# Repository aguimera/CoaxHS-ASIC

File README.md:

View this project on [CADLAB.io](https://cadlab.io/project/27561). 

# CoaxHS-ASIC

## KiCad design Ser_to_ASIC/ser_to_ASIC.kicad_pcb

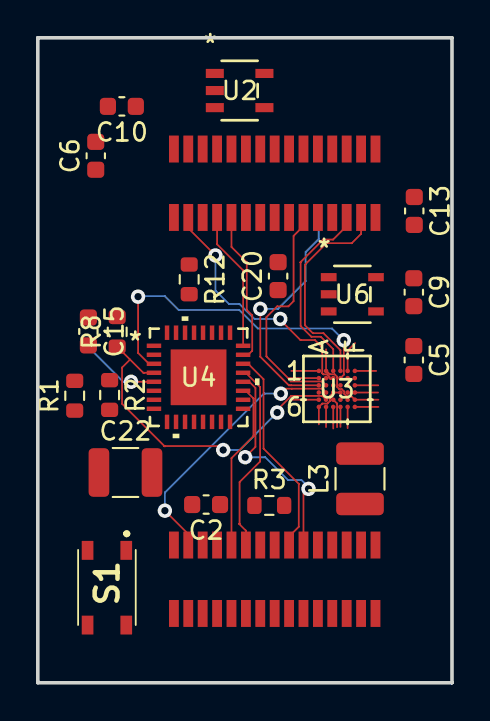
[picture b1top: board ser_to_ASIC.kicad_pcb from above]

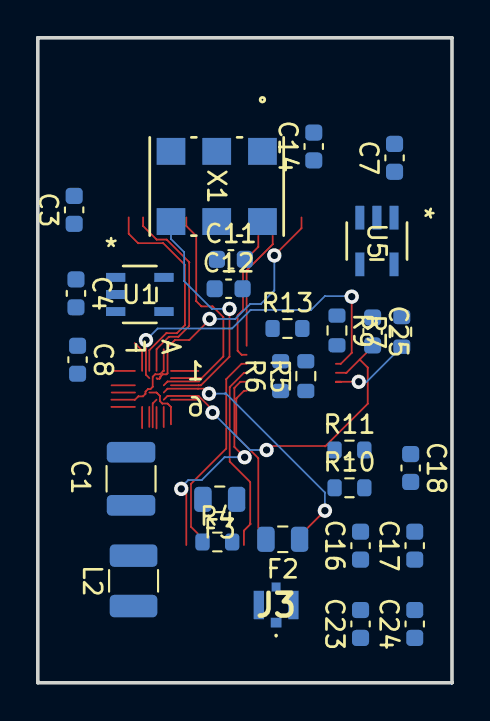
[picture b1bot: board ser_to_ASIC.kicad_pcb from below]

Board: 2 copper layers, 23.0 x 35.8 mm, 51 parts (29 on the bottom side), 47 nets.

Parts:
C1: 47uF; C_1210_3225Metric
C2, C12, C17, C24, C25: 0.1uF; C_0603_1608Metric
C3, C4, C5, C6, C7, C9, C11, C15, C16, C20, C23: 1uF; C_0603_1608Metric
C8, C10, C18: 10uF; C_0603_1608Metric
C13, C14: 0.01uF; C_0603_1608Metric
C22: 22uF; C_1210_3225Metric
F2, F3: 1000 ohm; Fuse_0805_2012Metric
J3: CONMHF4-SMD-G-T; CONMHF4SMDGT
J6, J200: MOLEX-524653071; J524653071_Board2Board
L2: 0.1 uF; L_1210_3225Metric
L3: 4.7 uF; L_1210_3225Metric
R1, R5, R10, R11: 10k; R_0603_1608Metric
R2: 100k; R_0603_1608Metric
R3, R4: 1k; R_0603_1608Metric
R6, R9, R12, R13: 0; R_0603_1608Metric
R7, R8: 4.7k; R_0603_1608Metric
S1: PTS810SJM250SMTRLFS; PTS810SJG250SMTRLFS
U1: ADP160AUJZ-1.2-R7; UJ_5_ADI
U2: ADP121-AUJZ12R7; UJ-5_ADI
U3: 10M02DCV36I7G; VBGA&slash_WLCSP36_A0p54_INT
U4: DS90UB913ATRTVJQ1; RTV32_3P1X3P1_TEX
U5: TC2015-1.8VCTTR; SOT-23-5_MC_MCH
U6: LT1761ES5-3.3-TRPBF; 05-08-1635_ADI
X1: EG-2102CA 100.0000M-PHPAL3; EG-2121CA_EPS

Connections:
+1V2: C6.1, U2.5 (VOUT), U3.B1 (VCC), U3.F5 (VCC)
+1V8: C5.1, C8.1, C11.1, C12.1, C14.1, C15.2, C16.1, C17.1, C20.1, C22.1, C23.1, C24.1, C25.2, R1.2, R5.2, U2.1 (VIN), U2.3 (EN), U4.10 (VDDPLL), U4.11 (VDDT), U4.14 (VDDCML), U4.25 (VDDIO), U4.28 (VDDD), U5.5
+3.3V: C7.1, C10.1, C13.1, R9.1, R10.1, R11.1, U3.A1 (VCCA3), U3.A6 (VCCA2), U3.C4 (VCCIO1_2_8), U3.D4 (VCCIO3_5_6), U5.1, U5.3, U6.5 (OUT), X1.1 (OE), X1.6 (VCC)
+5V: C3.2, U1.1 (VIN), U1.3 (EN)
+5VD: C1.1, F3.2
/CLK_100: U3.A3 (IO), X1.4 (OUT)
/DAC_SCK: J200.13, U3.B6 (IO)
/DAC_SDI: J200.14, U3.B4 (IO)
/DOUT+: C2.2, U4.13 (DOUT+)
/M0_B: J200.2, U3.D6 (IO)
/M1_B: J200.3, U3.F4 (IO)
/MODE_0: J6.25, U3.A2 (IO)
/MODE_1: J6.17, U3.C2 (IO)
/OSC_CLK: J200.9, U3.E1 (IO)
/PB_0: J200.1, U3.E6 (IO)
/PB_1: J200.4, U3.C5 (IO)
/SCLK: J200.8, U3.D2 (IO), U4.3 (PCLK)
/SCL_SER: R8.1, U3.B5 (IO), U4.4 (SCL)
/SDA_SER: R7.1, U3.A5 (IO), U4.5 (SDA)
/SER_B0: J200.11, U4.19 (DIN[0])
/SER_B1: J200.6, U4.20 (DIN[1])
/SER_B2: J200.10, U4.21 (DIN[2])
/SER_B3: J200.7, U4.22 (DIN[3])
/SER_B4: J6.20, U4.23 (DIN[4])
/SER_B5: J6.19, U4.24 (DIN[5])
/SER_B6: J6.21, U4.26 (DIN[6])
/SER_B7: J6.18, U4.27 (DIN[7])
/SER_CLK_0: J200.5, R13.1
/SER_CLK_1: J6.22, R12.1
/SPI_CLK: J6.29, U3.D1 (IO)
/SPI_DATA: J6.28, U3.C1 (IO)
/\DAC_CS: J200.12, U3.C6 (IO)
/\SPI_CS: J6.26, U3.F3 (IO)
G: C1.2, C3.1, C4.2, C5.2, C6.2, C7.2, C8.2, C9.2, C10.2, C11.2, C12.2, C15.1, C16.2, C17.2, C18.2, C20.2, C22.2, C23.2, C24.2, C25.1, J3.2 (GND_1), J3.3 (GND_2), J3.4 (GND_3), J6.1, J6.7, J6.8, J6.15, J6.16, J6.23, J6.24, J6.27, J6.30, J200.15, J200.16, R2.1, R6.2, R10.2, S1.1, S1.3, U1.2 (GND), U2.2 (GND), U3.B3 (GND), U3.F1 (GND), U3.F6 (GND), U4.7 (RES), U4.33 (EPAD), U5.2, U6.2 (GND), X1.3 (GND)
unnamed: C14.2, U5.4
unnamed: F2.2, L3.2, R4.2
unnamed: F3.1, L2.1, R3.1
unnamed: C2.1, F2.1, J3.1 (SIGNAL)
unnamed: L2.2, L3.1, R3.2, R4.1
unnamed: R7.2, R8.2, R9.2
unnamed: R12.2, U4.29 (DIN[8])
unnamed: R13.2, U4.30 (DIN[9])
unnamed: R5.1, R6.1, U4.6 (ID[X])
unnamed: R1.1, R2.2, U4.8 (MODE)
unnamed: C18.1, R11.2, S1.2, S1.4, U4.9 (PDB)
unnamed: C13.2, U6.4 (BYP)
VDC: C4.1, C9.1, U1.5 (VOUT), U6.1 (IN), U6.3 (*SHDN)

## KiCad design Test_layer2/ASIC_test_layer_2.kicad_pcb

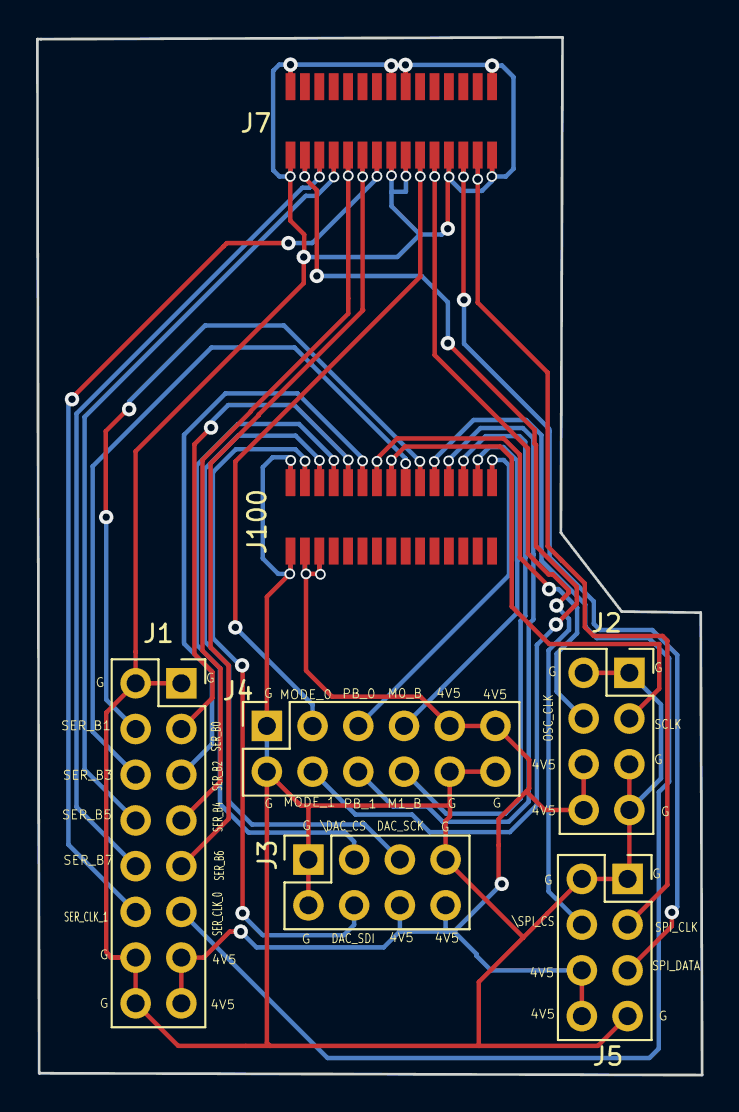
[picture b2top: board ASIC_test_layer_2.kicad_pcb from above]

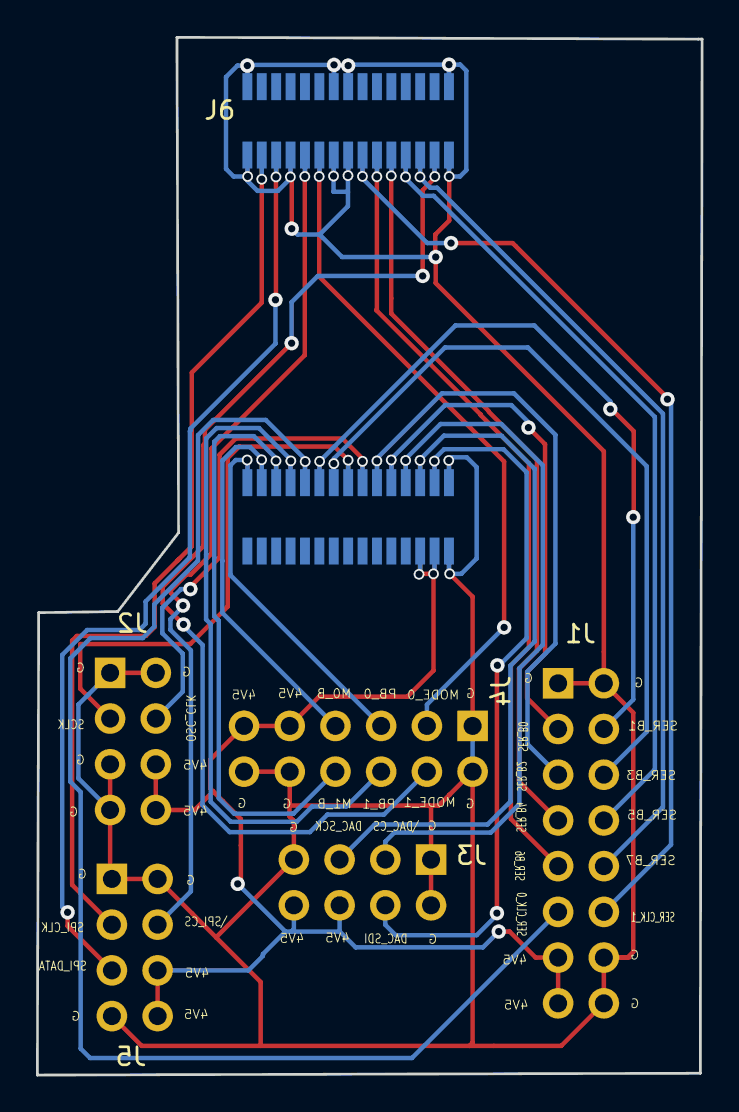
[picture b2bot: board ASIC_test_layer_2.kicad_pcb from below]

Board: 4 copper layers, 36.9 x 57.7 mm, 9 parts (2 on the bottom side), 26 nets.

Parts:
J1: Conn_02x08_Odd_Even; PinSocket_2x08_P2.54mm_Vertical
J2, J3, J5: Conn_02x04_Odd_Even; PinSocket_2x04_P2.54mm_Vertical
J4: Conn_02x06_Odd_Even; PinSocket_2x06_P2.54mm_Vertical
J6, J7, J100, J200: MOLEX-524653071; J524653071_Board2Board

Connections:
4V5: J1.13, J1.15, J2.6, J2.8, J3.6, J3.8, J4.9, J4.11, J5.6, J5.8, J100.28, J100.29, J200.17, J200.18
/DAC_SCK: J3.5, J100.3, J200.13
/DAC_SDI: J3.4, J100.2, J200.14
/M0_B: J4.7, J100.14, J200.2
/M1_B: J4.8, J100.13, J200.3
/MODE_0: J4.3, J6.25, J7.21
/MODE_1: J4.4, J6.17, J7.29
/OSC_CLK: J2.4, J100.7, J200.9
/PB_0: J4.5, J100.15, J200.1
/PB_1: J4.6, J100.12, J200.4
/SCLK: J2.3, J100.8, J200.8
/SER_B0: J1.3, J100.5, J200.11
/SER_B1: J1.4, J100.10, J200.6
/SER_B2: J1.5, J100.6, J200.10
/SER_B3: J1.6, J100.9, J200.7
/SER_B4: J1.7, J6.20, J7.26
/SER_B5: J1.8, J6.19, J7.27
/SER_B6: J1.9, J6.21, J7.25
/SER_B7: J1.10, J6.18, J7.28
/SER_CLK_0: J1.11, J100.11, J200.5
/SER_CLK_1: J1.12, J6.22, J7.24
/SPI_CLK: J5.3, J6.29, J7.17
/SPI_DATA: J5.5, J6.28, J7.18
/\DAC_CS: J3.3, J100.4, J200.12
/\SPI_CS: J5.4, J6.26, J7.20
G: J1.1, J1.2, J1.14, J1.16, J2.1, J2.2, J2.5, J2.7, J3.1, J3.2, J3.7, J4.1, J4.2, J4.10, J4.12, J5.1, J5.2, J5.7, J6.1, J6.7, J6.8, J6.15, J6.16, J6.23, J6.24, J6.27, J6.30, J7.1, J7.8, J7.9, J7.15, J7.16, J7.19, J7.22, J7.23, J7.30, J100.1, J100.30, J200.15, J200.16

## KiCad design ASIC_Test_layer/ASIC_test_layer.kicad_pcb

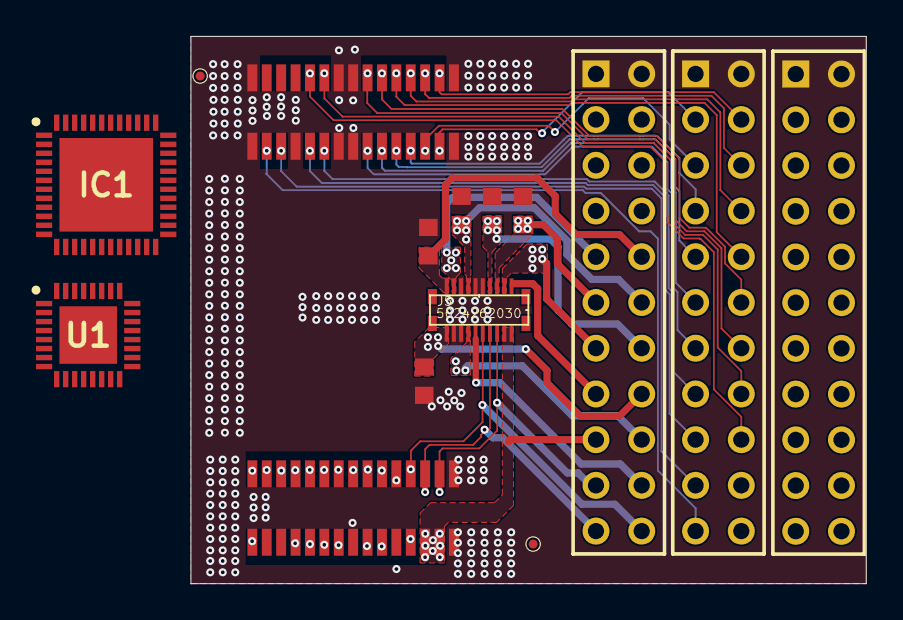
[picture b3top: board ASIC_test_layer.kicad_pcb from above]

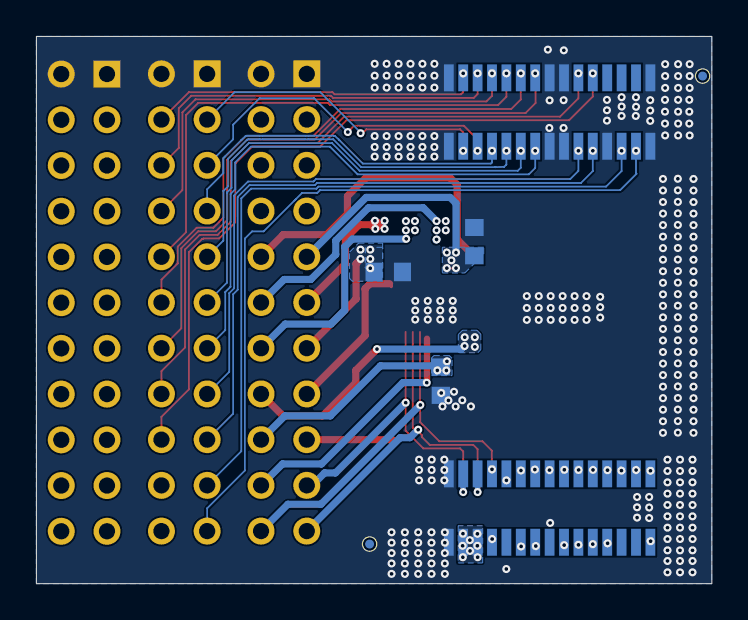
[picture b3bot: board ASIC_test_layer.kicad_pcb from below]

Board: 4 copper layers, 37.5 x 30.4 mm, 22 parts (7 on the bottom side), 52 nets.

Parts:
C200, C201, C202, C203, C204, C205, C206, C207: 10uF; CAPC1709X50N
FID1, FID2, FID3, FID4: FIDUCIAL; MFID0508
IC1: DS90UB914ATRHSJQ1; QFN50P700X700X80-49N
J5: 5024262030; JMOLEX-0559090274V1
J6, J7, J100, J200: MOLEX-524653071; J524653071_Board2Board
P11, P12, P13: Header 11X2; HDR2X11
U1: DS90UB913ATRTVTQ1; QFN50P500X500X80-33N

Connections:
4V5: J5.2, J5.4, J100.17, J100.18, J200.28, J200.29, P11.17
/B_MODE_0: J6.10, J7.6, P12.16
/B_MODE_1: J6.2, J7.14, P12.4
/B_PB_0: J100.30, J200.16
/B_PB_1: J100.27, J200.19
/B_SER_B0: J100.21, J200.25, P13.20
/B_SER_B1: J100.25, J200.21
/B_SER_B2: J100.22, J200.24, P13.18
/B_SER_B3: J100.24, J200.22
/B_SER_B4: J6.5, J7.11, P12.10
/B_SER_B5: J6.4, J7.12, P12.8
/B_SER_B6: J6.6, J7.10, P12.12
/B_SER_B7: J6.3, J7.13, P12.6
/B_SER_CLK_0: J100.26, J200.20
/B_SER_CLK_1: J6.7, J7.9, P12.14
/DAC_SCK: J5.8, J100.13, J200.3, P11.21
/DAC_SDI: J5.6, J100.14, J200.2, P11.19
/M0_B: J100.2, J200.14, P13.5
/M1_B: J100.3, J200.13, P13.7
/MODE_0: J6.21, J7.25, P12.15
/MODE_1: J6.29, J7.17, P12.3
/OSC_CLK: J100.9, J200.7, P13.16
/PB_0: J100.1, J200.15, P13.3
/PB_1: J100.4, J200.12, P13.9
/SCLK: J100.8, J200.8, P13.17
/SER_B0: J100.11, J200.5, P13.21
/SER_B1: J100.6, J200.10, P13.13
/SER_B2: J100.10, J200.6, P13.19
/SER_B3: J100.7, J200.9, P13.15
/SER_B4: J6.26, J7.20, P12.9
/SER_B5: J6.27, J7.19, P12.7
/SER_B6: J6.25, J7.21, P12.11
/SER_B7: J6.28, J7.18, P12.5
/SER_CLK_0: J100.5, J200.11, P13.11
/SER_CLK_1: J6.24, J7.22, P12.13
/SPI_CLK: J6.17, J7.29, P12.21
/SPI_DATA: J6.18, J7.28, P12.19
/\B_DAC_CS: J100.19, J200.27, P13.22
/\B_SPI_CS: J6.11, J7.5, P12.18
/\DAC_CS: J5.10, J100.12, J200.4, P11.22
/\SPI_CS: J6.20, J7.26, P12.17
BATH: J5.12, P11.20
G: C200.2, C201.2, C202.2, C203.2, C204.2, C205.2, C206.2, C207.2, J5.9, J5.11, J5.15, J5.16, J5.18, J6.1, J6.8, J6.9, J6.15, J6.16, J6.19, J6.22, J6.23, J6.30, J7.1, J7.7, J7.8, J7.15, J7.16, J7.23, J7.24, J7.27, J7.30, J100.15, J100.16, J200.1, J200.30, P11.1, P11.2, P12.1, P12.2, P13.1, P13.2
VCM: C202.1, J5.17, P11.9
VDD_1V2: J5.1, P11.15
VDD_A: C200.1, J5.19, P11.10
VDD_D: C201.1, J5.3, P11.13
VREF_C: C203.1, J5.14, P11.18
VREF_COL: C205.1, J5.20, P11.16
VREF_E: C206.1, J5.13, P11.12
VREF_H: C204.1, J5.7, P11.14
VREF_L: C207.1, J5.5, P11.11

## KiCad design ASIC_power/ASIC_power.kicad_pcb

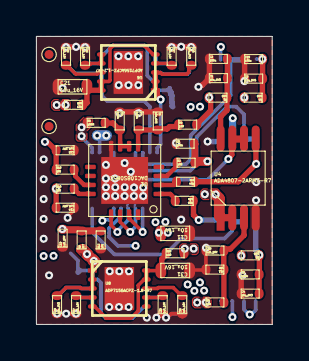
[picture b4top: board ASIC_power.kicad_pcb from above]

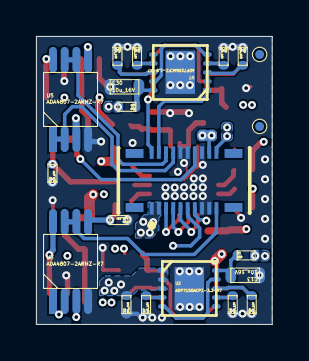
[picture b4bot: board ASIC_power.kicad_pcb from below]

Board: 6 copper layers, 13.1 x 16.0 mm, 68 parts (21 on the bottom side), 45 nets.

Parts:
C1, C4, C6, C9, C12, C20, C28, C29: 10u_6V3; C0402
C2, C3, C5, C7, C8, C10: 100n; C0402
C11, C13, C21, C30, C31: 10u_16V; C0603
C14, C15, C16, C17, C18, C19, C22, C23, C24, C25, C26, C27, C32, C33, C34, C35, C36, C37: 1u0_10V; C0402
FID1, FID2, FID3, FID4: FIDUCIAL; MFID0508
J10: 51338-0274; FP-51338-0274-MFG
R1, R2, R3, R6, R7, R13, R19, R20: 1R0; R0402
R4: 10R; R0402
R5: 100R; R0402
R8, R10, R11, R12, R14, R15, R16: 10k; R0402
R9: 2k7; R0402
U1: DAC108S085C; UWQFN16H-0.5
U2: ADP7156ACPZ-3.3-R7; ULFCSP10
U3, U4, U5: ADA4807-2ARMZ-R7; UMSOP8
U6: ADP7156ACPZ-1.2-R7; ULFCSP10
U7, U8: ADP7156ACPZ-1.8-R7; ULFCSP10

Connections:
3V3: C12.2, R1.2, R3.2, R4.2, R6.2, U2.1 (VOUT), U2.2 (VOUT), U2.3 (VS)
4V5: C11.2, J10.1, J10.3, R7.2, R13.2, R19.2, R20.2
BATH: C3.2, J10.11, R2.2
G: C1.1, C2.1, C3.1, C4.1, C5.1, C6.1, C7.1, C8.1, C9.1, C10.1, C11.1, C12.1, C13.1, C14.1, C15.1, C16.1, C17.1, C18.1, C19.1, C20.1, C21.1, C22.1, C23.1, C24.1, C25.1, C26.1, C27.1, C28.1, C29.1, C30.1, C31.1, C32.1, C33.1, C34.1, C35.1, C36.1, C37.1, J10.10, J10.12, J10.15, J10.16, J10.17, R11.2, R12.1, U1.8 (G), U2.0 (GND), U3.4 (V-), U4.4 (V-), U5.4 (V-), U6.0 (GND), U7.0 (GND), U8.0 (GND)
unnamed: C6.2, C7.2, R4.1, U1.5 (VA)
unnamed: R2.1, U1.3 (VoutC)
unnamed: C8.2, R5.2, U1.6 (Vref1), U1.7 (Vref2)
unnamed: C17.2, U2.4 (BYP)
unnamed: C13.2, R7.1, U2.5 (EN), U2.9 (VIN), U2.10 (VIN)
unnamed: C15.2, U2.6 (Sense), U2.7 (REF)
unnamed: C16.2, U2.8 (VREG)
unnamed: C19.2, R9.2, R12.2, U3.3 (+IN)
unnamed: C24.2, R16.1, U3.5 (+IN2)
unnamed: C18.2, R8.2, R11.1, U4.3 (+IN)
unnamed: C22.2, R14.1, U4.5 (+IN2)
unnamed: C14.2, R10.1, U5.3 (+IN)
unnamed: C23.2, R15.1, U5.5 (+IN2)
unnamed: C27.2, U6.4 (BYP)
unnamed: C21.2, R13.1, U6.5 (EN), U6.9 (VIN), U6.10 (VIN)
unnamed: C25.2, U6.6 (Sense), U6.7 (REF)
unnamed: C26.2, U6.8 (VREG)
unnamed: C36.2, U7.4 (BYP)
unnamed: C30.2, R19.1, U7.5 (EN), U7.9 (VIN), U7.10 (VIN)
unnamed: C32.2, U7.6 (Sense), U7.7 (REF)
unnamed: C34.2, U7.8 (VREG)
unnamed: C37.2, U8.4 (BYP)
unnamed: C31.2, R20.1, U8.5 (EN), U8.9 (VIN), U8.10 (VIN)
unnamed: C33.2, U8.6 (Sense), U8.7 (REF)
unnamed: C35.2, U8.8 (VREG)
SUP_A: C1.2, C2.2, R1.1, U4.8 (V+)
SUP_B: C4.2, C5.2, R3.1, U3.8 (V+)
SUP_C: C9.2, C10.2, R6.1, U5.8 (V+)
VCM: J10.18, U4.1 (OUT), U4.2 (-IN)
VDD_1V2: C20.2, J10.2, U6.1 (VOUT), U6.2 (VOUT), U6.3 (VS)
VDD_A: C29.2, J10.20, R5.1, R8.1, R9.1, U8.1 (VOUT), U8.2 (VOUT), U8.3 (VS)
VDD_D: C28.2, J10.4, U7.1 (VOUT), U7.2 (VOUT), U7.3 (VS)
VREF_C: J10.13, U3.1 (OUT), U3.2 (-IN)
VREF_COL: J10.19, U3.6 (IN2), U3.7 (OUT)
VREF_COL': R16.2, U1.1 (VoutA)
VREF_E: J10.14, U4.6 (IN2), U4.7 (OUT)
VREF_E': R14.2, U1.2 (VoutB)
VREF_H: J10.8, U5.1 (OUT), U5.2 (-IN)
VREF_H': R10.2, U1.12 (VoutE)
VREF_L: J10.6, U5.6 (IN2), U5.7 (OUT)
VREF_L': R15.2, U1.11 (VoutF)

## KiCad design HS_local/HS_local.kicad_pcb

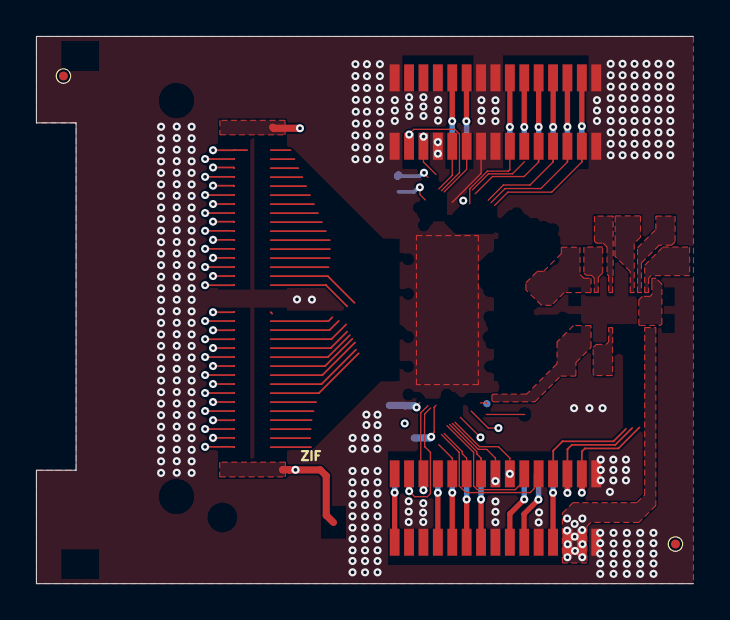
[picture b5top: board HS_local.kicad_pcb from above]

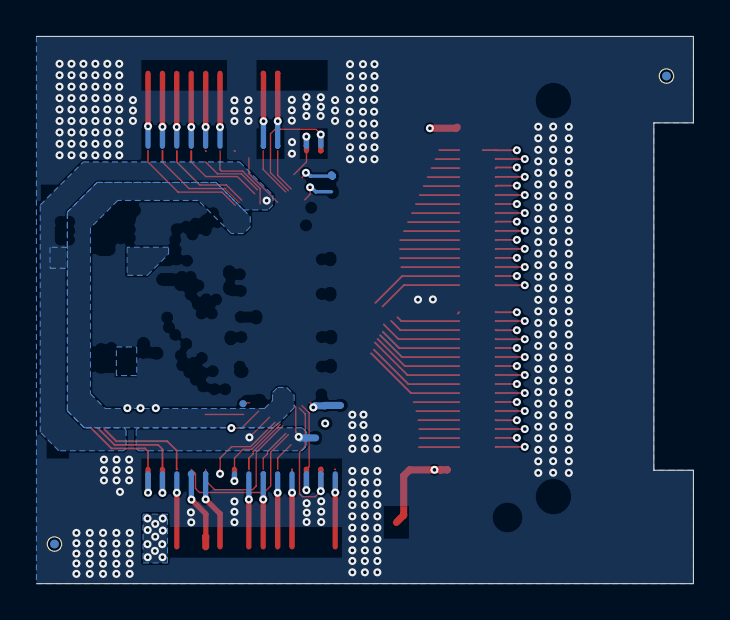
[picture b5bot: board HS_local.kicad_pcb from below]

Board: 6 copper layers, 36.5 x 30.4 mm, 6 parts (2 on the bottom side), 2 nets.

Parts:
FID1, FID2, FID3, FID4: FIDUCIAL; MFID0508
J6: MOLEX-524653071; J524653071_Board2Board
J200: MOLEX-524653071; J524653071

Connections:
4V5: J200.28, J200.29
G: J6.1, J6.8, J6.9, J6.15, J6.16, J6.19, J6.22, J6.23, J6.30, J200.1, J200.30

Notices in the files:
parts and their libraries:
COPYRIGHT: Copyright (C) 2022 Ultra Librarian. All rights reserved.
